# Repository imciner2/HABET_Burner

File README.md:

HABET_Burner
============

Burner designed for High Altitude Ballooning

Housekeeping
============
This repository makes use of git subtrees for importing its KiCad libraries. Use the following commands to work with them
* To add the remote link: git remote add libraries https://github.com/imciner2/KiCad-Libraries.git
* To pull the newest version: git subtree pull --prefix Electronics/2-Hardware/libraries/ libraries master --squash
* To push the changes to the repo: git subtree push --prefix Electronics/2-Hardware/libraries/ libraries master

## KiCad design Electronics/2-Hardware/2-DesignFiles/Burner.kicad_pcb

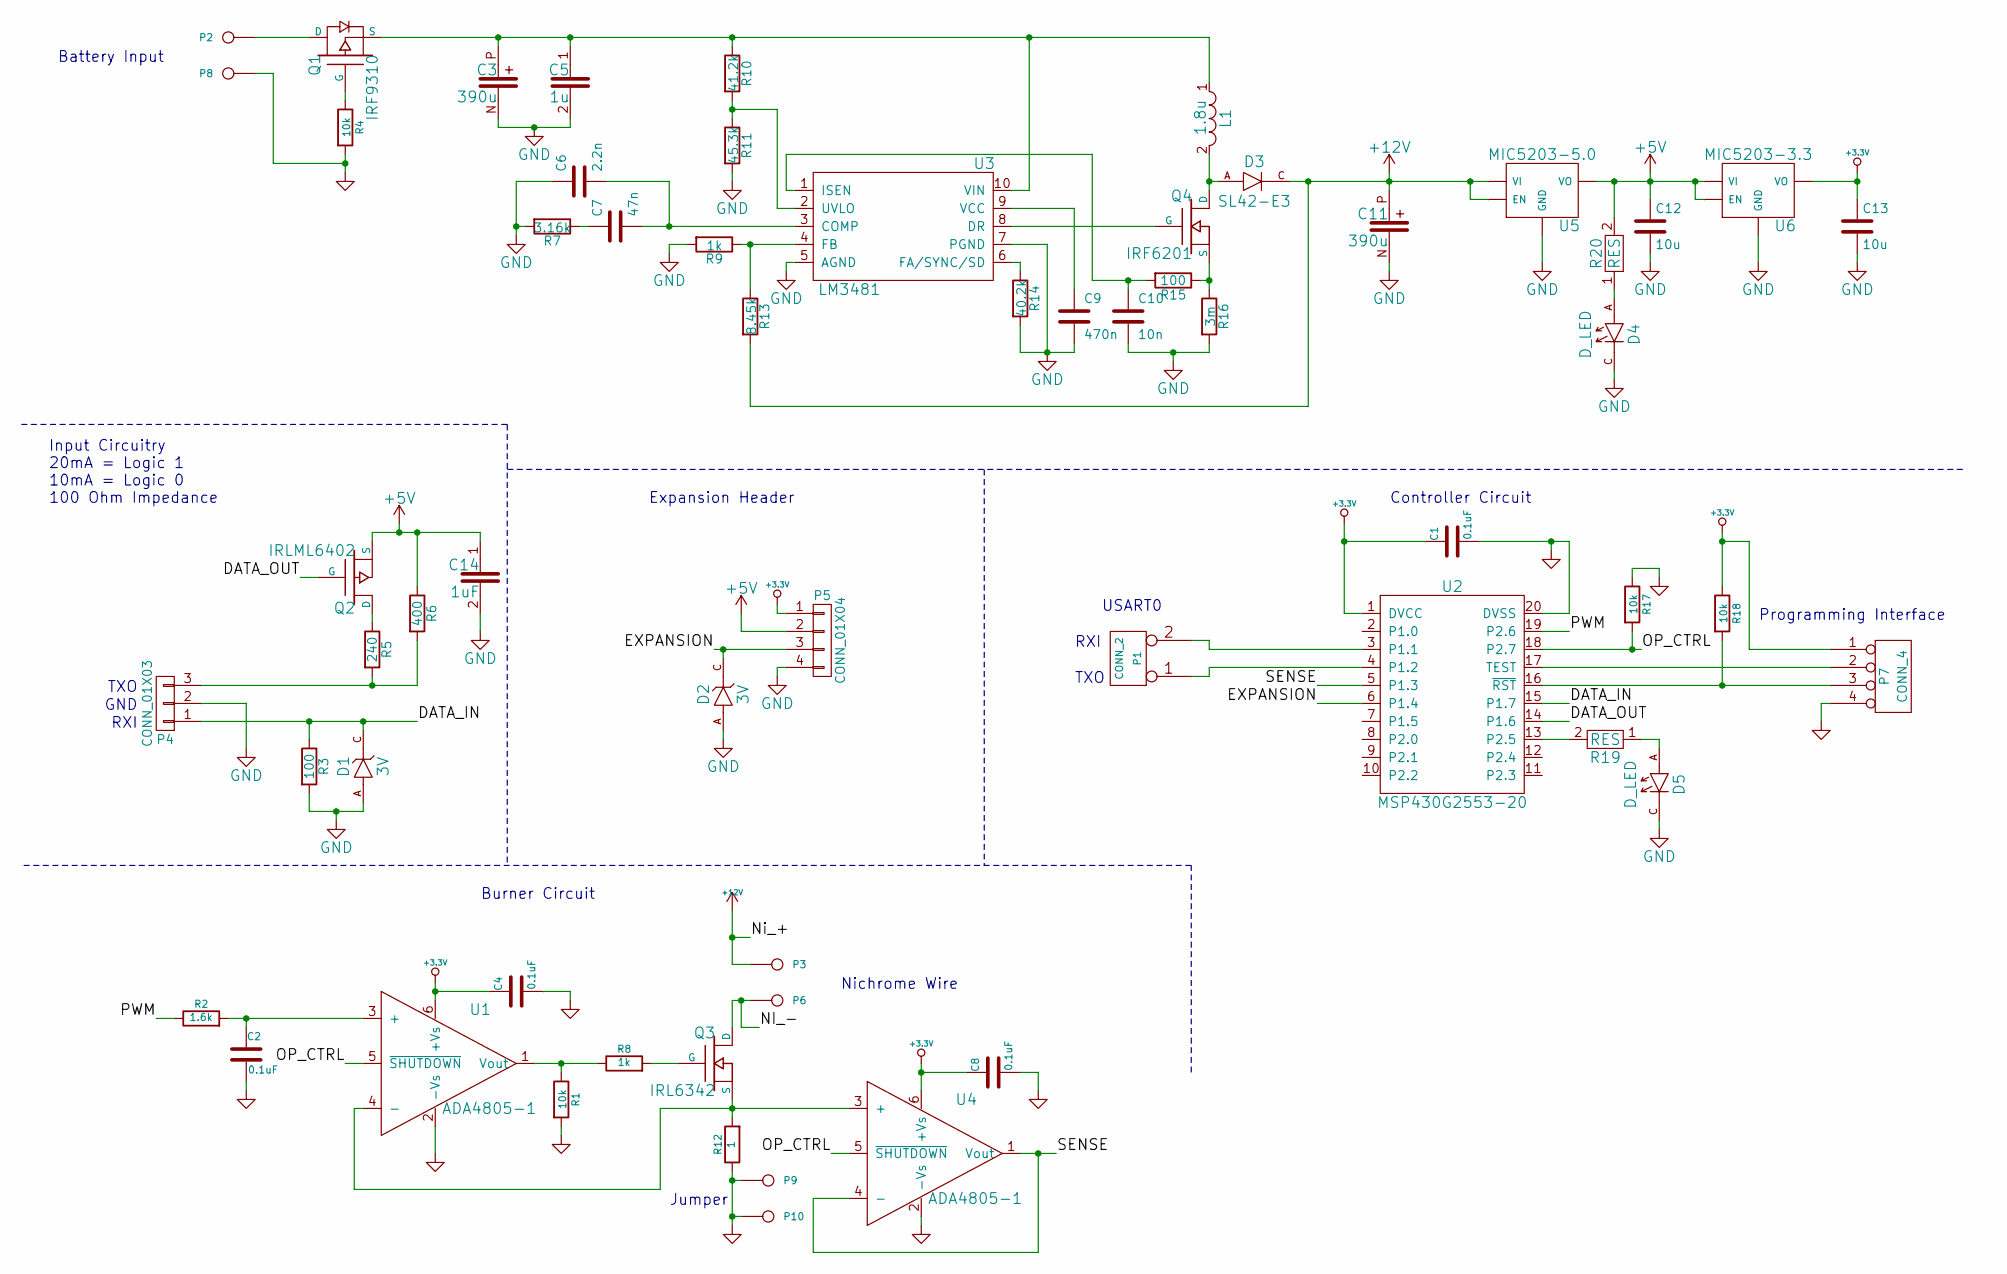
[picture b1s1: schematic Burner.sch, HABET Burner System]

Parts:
C1: 0.1uF; SMD_0805; DigikeyPart 311-1141-1-ND
C2, C4, C8: 0.1uF; SMD_0805
C3, C11: 390u; SMD_POL_E12_8.3mm
C5: 1u; SMD_0805
C6: 2.2n; SMD_0805
C7: 47n; SMD_0805
C9: 470n; SMD_0805
C10: 10n; SMD_0805
C12, C13: 10u; SMD_0805
C14: 1uF; SMD_0805
D1, D2: 3V; DIODE_SOT-23-3; DigikeyNumber BZX84C3V0LT1GOSCT-ND
D3: SL42-E3; DIODE_DO214AB-SMC; DigikeyNumber SL42-E3/57TGICT-ND
D4, D5: D_LED; LED_1206
L1: 1.8u; IND_BOURNS_SRP1238A; DigikeyNumber SRP1238A-1R8MCT-ND
P1: CONN_2; CONN_2.54mm_1x2
P2, P3, P6, P8, P9, P10: CONN_1; CONN_2.54mm_1x1
P4: CONN_01X03; CONN_2.54mm_1x3
P5: CONN_01X04; CONN_2.00mm_1x4
P7: CONN_4; CONN_2.54mm_1x4
Q1: IRF9310; TRANS_SO_4.0mm_1.27mm_8; DigikeyNumber IRF9310TRPBFCT-ND
Q2: IRLML6402; TRANS_SOT-23-3; DigikeyNumber IRLML6402PBFCT-ND
Q3: IRL6342; TRANS_SO_4.0mm_1.27mm_8; DigikeyNumber IRL6342TRPBFCT-ND
Q4: IRF6201; TRANS_SO_4.0mm_1.27mm_8; DigikeyNumber IRF6201TRPBFCT-ND
R1: 10k; SMD_0805; DigikeyPart P10.0KCCT-ND
R2: 1.6k; SMD_0805
R3, R15: 100; SMD_0805
R4, R17, R18: 10k; SMD_0805
R5: 240; SMD_0805
R6: 400; SMD_0805
R7: 3.16k; SMD_0805
R8, R9: 1k; SMD_0805
R10: 41.2k; SMD_0805
R11: 45.3k; SMD_0805
R12: 1; RES_D2PACK; DigikeyNumber PWR163S-25-1R00J-ND
R13: 8.45k; SMD_0805
R14: 40.2k; SMD_0805
R16: 3m; SMD_2010; DigikeyNumber RHM.003ASCT-ND
R19, R20: RES; SMD_0805
U1, U4: ADA4805-1; SOT-23-6; DigikeyNumber ADA4805-1ARJZ-R7CT-ND
U2: MSP430G2553-20; SOP_4.5mm_0.65mm_20; DigikeyPart 296-28430-1-ND
U3: LM3481; SOP_3.0mm_0.5mm_10; DigikeyNumber LM3481MM/NOPBCT-ND
U5: MIC5203-5.0; SOT-23-5; DigikeyPart 576-2734-1-ND
U6: MIC5203-3.3; SOT-23-5; DigikeyNumber 576-2728-1-ND

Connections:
+3.3V: C1.1, C4.1, C8.1, C13.1, P5.1, P7.1, R18.1, U1.6 (+Vs), U2.1 (DVCC), U4.6 (+Vs), U6.5 (VO)
+5V: C12.1, C14.1, P5.2, Q2.S, R6.1, R20.2, U5.5 (VO), U6.1 (VI), U6.3 (EN)
+12V: C11.P, D3.C, P3.1, R13.2, U5.1 (VI), U5.3 (EN)
/DATA_IN: D1.C, P4.1, R3.1, U2.15 (P1.7)
/DATA_OUT: Q2.G, U2.14 (P1.6)
/EXPANSION: D2.C, P5.3, U2.6 (P1.4)
/NI_-: P6.1, Q3.D
/OP_CTRL: R17.2, U1.5 (~SHUTDOWN), U2.18 (P2.7), U4.5 (~SHUTDOWN)
/PWM: R2.1, U2.19 (P2.6)
/SENSE: U2.5 (P1.3), U4.1 (Vout), U4.4 (-)
GND: C1.2, C2.2, C3.N, C4.2, C5.2, C6.1, C8.2, C9.2, C10.2, C11.N, C12.2, C13.2, C14.2, D1.A, D2.A, D4.C, D5.C, P4.2, P5.4, P7.4, P8.1, P9.1, P10.1, R1.2, R3.2, R4.2, R7.2, R9.2, R11.2, R12.1, R14.2, R16.2, R17.1, U1.2 (-Vs), U2.20 (DVSS), U3.5 (AGND), U3.7 (PGND), U4.2 (-Vs), U5.2 (GND), U6.2 (GND)
unnamed: C2.1, R2.2, U1.3 (+)
unnamed: C3.P, C5.1, L1.1, Q1.S, R10.1, U3.10 (VIN)
unnamed: C6.2, C7.2, U3.3 (COMP)
unnamed: C7.1, R7.1
unnamed: C9.1, U3.9 (VCC)
unnamed: C10.1, R15.2, U3.1 (ISEN)
unnamed: D3.A, L1.2, Q4.D
unnamed: D4.A, R20.1
unnamed: D5.A, R19.1
unnamed: P1.1, U2.4 (P1.2)
unnamed: P1.2 (PM), U2.3 (P1.1)
unnamed: P2.1, Q1.D
unnamed: P4.3, R5.2, R6.2
unnamed: P7.2, U2.17 (TEST)
unnamed: P7.3, R18.2, U2.16 (~RST~)
unnamed: Q1.G, R4.1
unnamed: Q2.D, R5.1
unnamed: Q3.G, R8.2
unnamed: Q3.S, R12.2, U1.4 (-), U4.3 (+)
unnamed: Q4.G, U3.8 (DR)
unnamed: Q4.S, R15.1, R16.1
unnamed: R1.1, R8.1, U1.1 (Vout)
unnamed: R10.2, R11.1, U3.2 (UVLO)
unnamed: R9.1, R13.1, U3.4 (FB)
unnamed: R14.1, U3.6 (FA/SYNC/SD)
unnamed: R19.2, U2.13 (P2.5)

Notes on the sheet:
RXI
TXO
USART0
Nichrome Wire
Burner Circuit
Controller Circuit
Programming Interface
Input Circuitry 20mA = Logic 1 10mA = Logic 0 100 Ohm Impedance
Battery Input
GND
Expansion Header
Jumper

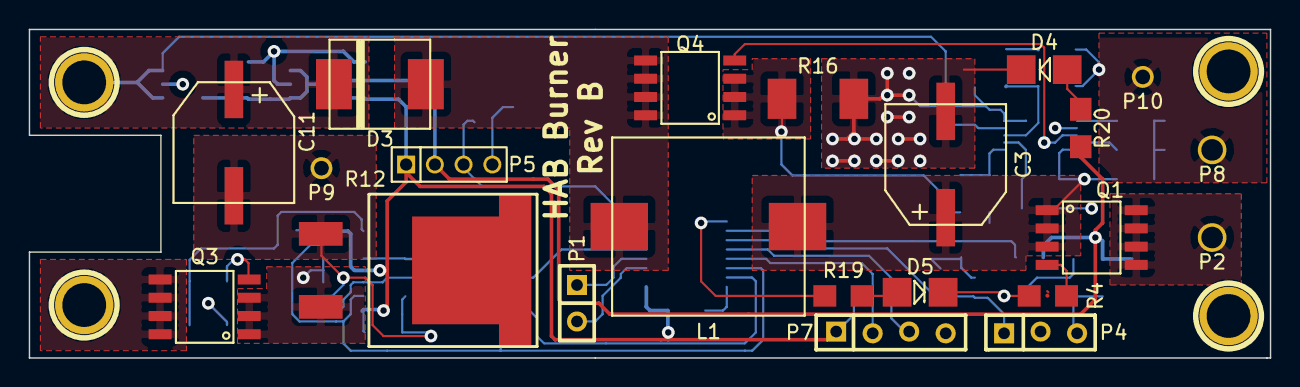
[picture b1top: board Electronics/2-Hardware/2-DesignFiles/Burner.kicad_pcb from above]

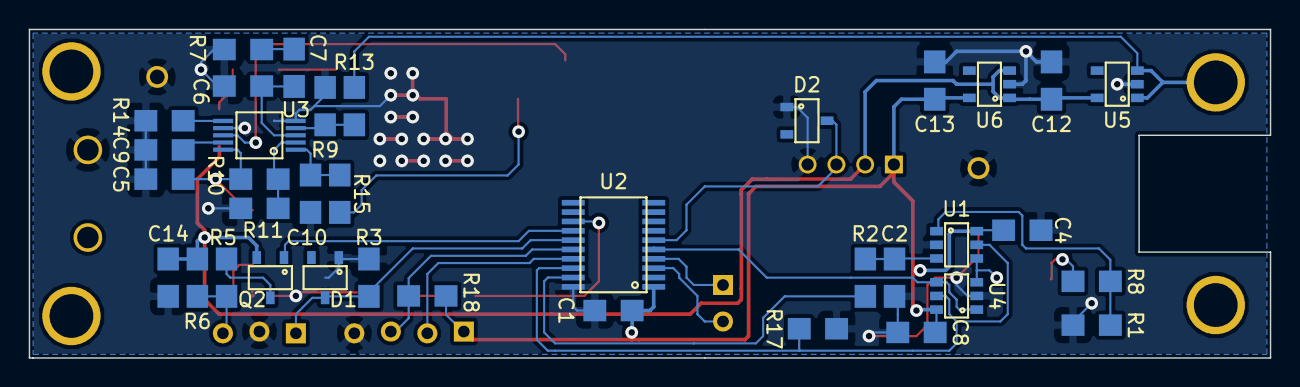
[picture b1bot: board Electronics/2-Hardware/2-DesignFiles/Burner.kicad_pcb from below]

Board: 2 copper layers, 86.4 x 22.9 mm, 62 parts (36 on the bottom side), 37 nets.

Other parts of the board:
1PIN, 1PIN#2: P***; 1pin

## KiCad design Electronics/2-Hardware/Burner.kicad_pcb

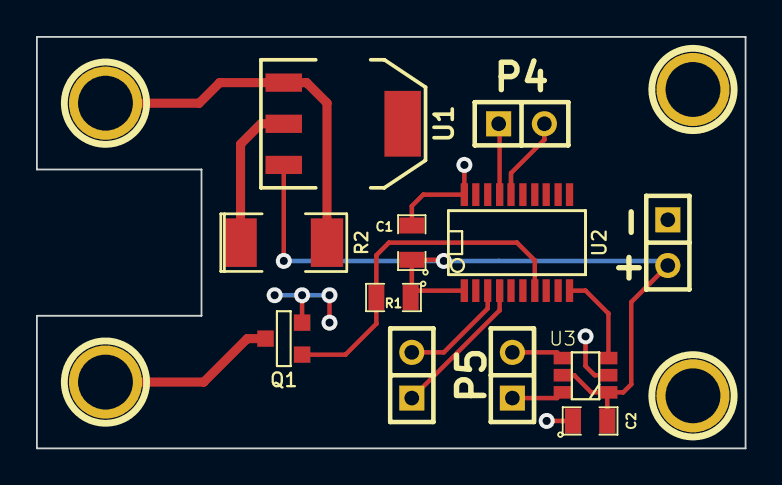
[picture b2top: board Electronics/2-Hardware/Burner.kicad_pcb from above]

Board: 2 copper layers, 39.4 x 22.9 mm, 16 parts (0 on the bottom side), 13 nets.

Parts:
1PIN, 1PIN#2: P***; 1pin
C1: 1uF; SM0805
C2: 0.1uF; SM0805
P1, P2, P4, P5: CONN_2; CONN_1x2
P3, P6: CONN_1; 1pin
Q1: MOSFET_N; SOT23GDS
R1: 10k; SM0805
R2: 2.7; SM2010
U1: LM317-4PIN; SOT223
U2: MSP430G2553-20; SSOP20
U3: DIFF_RX; SOT23_6

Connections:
+BATT: C1.1, C2.2, P2.2, R1.1, U1.3, U2.1, U3.1, U3.5
/DATA_IN: U2.10, U3.3
/MOS_TRIG: Q1.G, R1.2, U2.7
/NI_-: P6.1, Q1.D
/NI_Out: R2.1, U1.2
/Ni_+: P3.1, R2.2, U1.1
GND: C1.2, C2.1, P2.1, Q1.S, U2.20, U3.2
unnamed: P4.2, U2.16
unnamed: P5.1, U3.6
unnamed: P5.2, U3.4
unnamed: P1.2, U2.3
unnamed: P1.1, U2.4
unnamed: P4.1, U2.17

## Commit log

2014-04-21 Initial commit of revision A electronics.
2015-02-18 Squashed 'Electronics/2-Hardware/libraries/' content from commit 55d656b
    git-subtree-dir: Electronics/2-Hardware/libraries
    git-subtree-split: 55d656bbbc44133183b656e17598b3c6db58abac
2015-02-18 Added datasheets for new parts
2015-02-18 Added opamp and DAC
2015-02-18 Updated library readme
2015-02-18 Started new design. Fixes #1, fixes #4, fixes #6.
2015-02-18 Updated readme with some subtree stuff
2015-02-25 Added TI LM3481
2015-02-25 Added boost convertor to schematic
2015-02-25 Updated subtree in readme
2015-02-28 Changed DAC to be a LPF style
2015-03-12 Updated file structure
2015-03-12 Added MOSFETs with body diodes
2015-03-12 Updated reverse battery protection
2015-03-12 Updated KiCad library
2015-03-14 Added pin numbers to ADA4805, updated part fields
2015-03-14 Split out power components into their own library
2015-03-15 Update to include Kicad symbol descriptions
2015-03-15 Updated to include component descriptions
2015-03-15 Datasheet for the Boost controller
2015-03-15 Updated symbols on schematic
2015-03-15 Fixing subtree issues
2015-03-15 Squashed 'Electronics/2-Hardware/2-DesignFiles/libraries/' content from commit d0926fd
    git-subtree-dir: Electronics/2-Hardware/2-DesignFiles/libraries
    git-subtree-split: d0926fdb5d0c4087c46e7bebfcc138c84b1108ec
2015-03-15 Updated library components
2015-03-16 Boost converter Webench design
2015-03-17 Updated MOSFETs to be NMOS and PMOS
2015-03-17 Added input circuitry, expansion port, power rails
2015-03-17 Squashed 'Electronics/2-Hardware/2-DesignFiles/libraries/' changes from d0926fd..2f8a1ce
    2f8a1ce Updated library components
    git-subtree-dir: Electronics/2-Hardware/2-DesignFiles/libraries
    git-subtree-split: 2f8a1ce732415647da39b57d53ef19bd840fbb1a
2015-03-17 Footprints table for this board
2015-03-18 Added new datasheets
2015-03-18 Created custom diode symbols
2015-03-18 Updated field visibility
2015-03-18 Added new regulator type
2015-03-18 Started new footprints library structure
2015-03-18 Worked on component footprint matching
2015-03-18 Created passive symbols
2015-03-18 Created capacitor footprint
2015-03-18 Updated footprint association for capacitors
2015-03-18 Updated schematic and footprint association
2015-03-18 Added SL42 diode footprint
2015-03-18 Added Bourns SRP1238 footprint
2015-03-18 Added diode and inductor for Boost converter
2015-03-23 Updated schematic with LEDs, created board layout
2015-03-23 Manufacturing outputs
2015-03-23 Added more libraries
2015-03-23 Added new footprints libraries
2015-03-23 Datasheet
2015-03-23 Updated to ignore board backup file
2015-03-23 Remove board backup file
2015-03-23 Squashed 'Electronics/2-Hardware/2-DesignFiles/libraries/' changes from 2f8a1ce..da61080
    da61080 Added Bourns SRP1238 footprint
    6299f52 Added SL42 diode footprint
    6ec2c69 Created capacitor footprint
    8325f01 Created passive symbols
    315c38a Started new footprints library structure
    71c689a Added new regulator type
2015-03-23 Removed duplicate footprints
2015-03-23 Squashed 'Electronics/2-Hardware/2-DesignFiles/libraries/' changes from da61080..0f7fcab
    0f7fcab Parts for 0805, 1206, 2010 passives
    6a5b829 Instructions for 3D part creation
    b08d95c Removed duplicate footprints
    9cf71d1 Pulled the library
    511c9aa Added new footprints libraries
    git-subtree-dir: Electronics/2-Hardware/2-DesignFiles/libraries
2015-03-24 Moved parts to fix zone encroachment
2015-03-25 Fixed back silkscreen
2015-03-25 Moved some references on the bottom
2015-03-25 Changed drill file to have zeros
2015-03-25 Board pictures from OSHpark
2015-04-08 Updated component part numbers
2015-04-08 Final circuit information for Rev B
2015-04-20 Changed transconductance op-amp power supply. Reorganized schematic
2015-04-20 Added pictures of specific parts of the circuit.
2015-04-20 Added pictures of specific parts of the circuit
2015-04-20 O-scope captures of the DAC in action
2015-04-20 Graph showing transfer characteristics of the amplifier
2015-04-22 Changed font size on transfer characteristics graph
2015-04-22 Changed font size on transfer function characteristics graph
2016-02-23 Updated PDF Schematic
